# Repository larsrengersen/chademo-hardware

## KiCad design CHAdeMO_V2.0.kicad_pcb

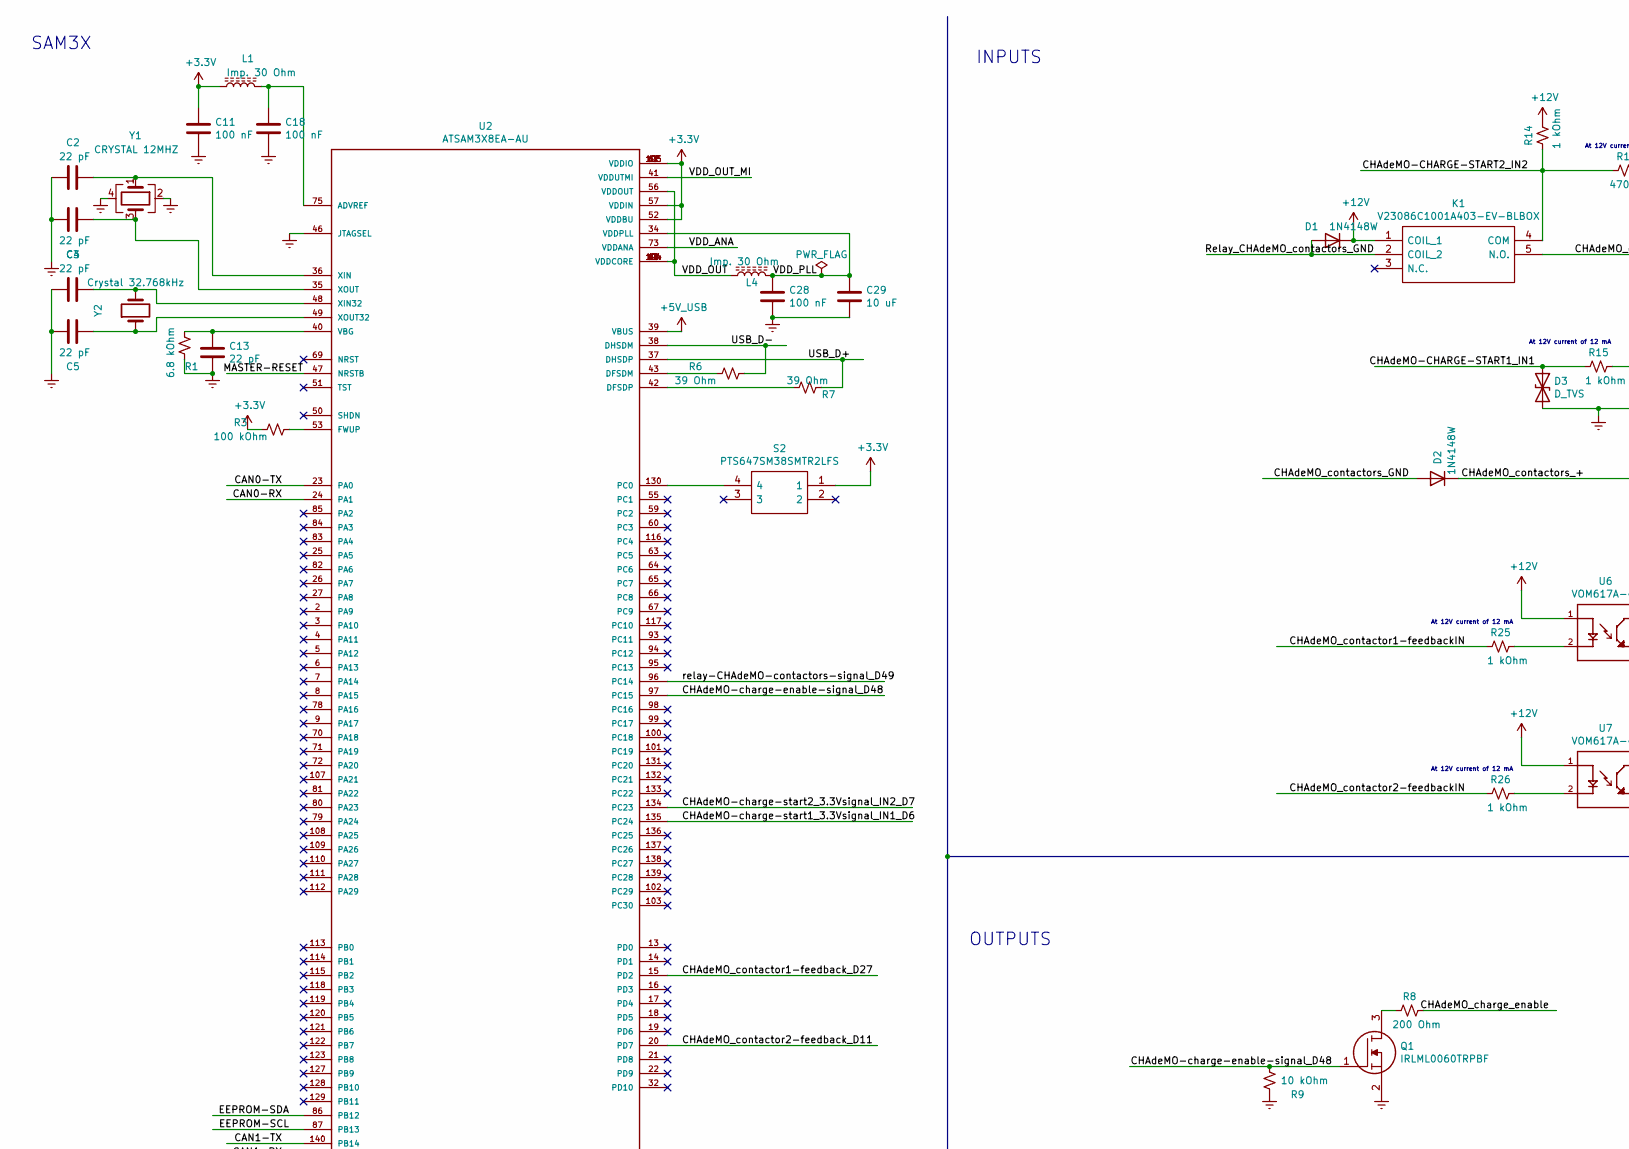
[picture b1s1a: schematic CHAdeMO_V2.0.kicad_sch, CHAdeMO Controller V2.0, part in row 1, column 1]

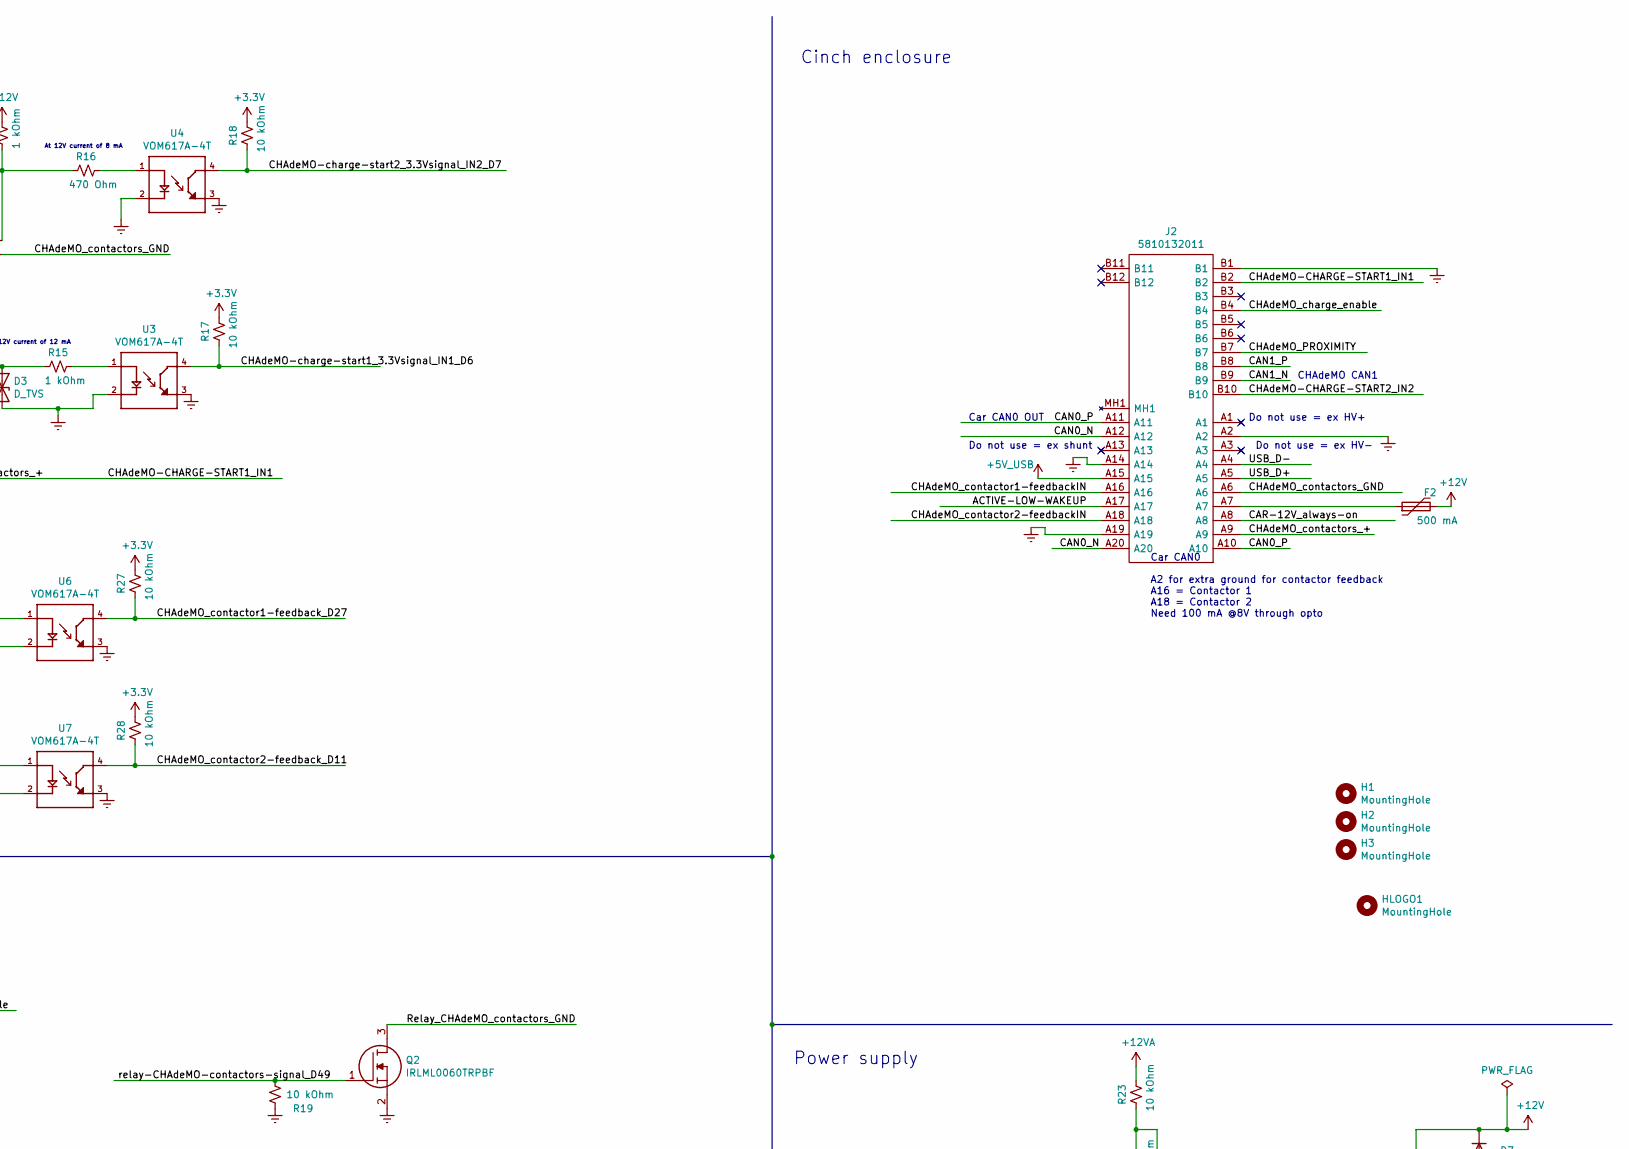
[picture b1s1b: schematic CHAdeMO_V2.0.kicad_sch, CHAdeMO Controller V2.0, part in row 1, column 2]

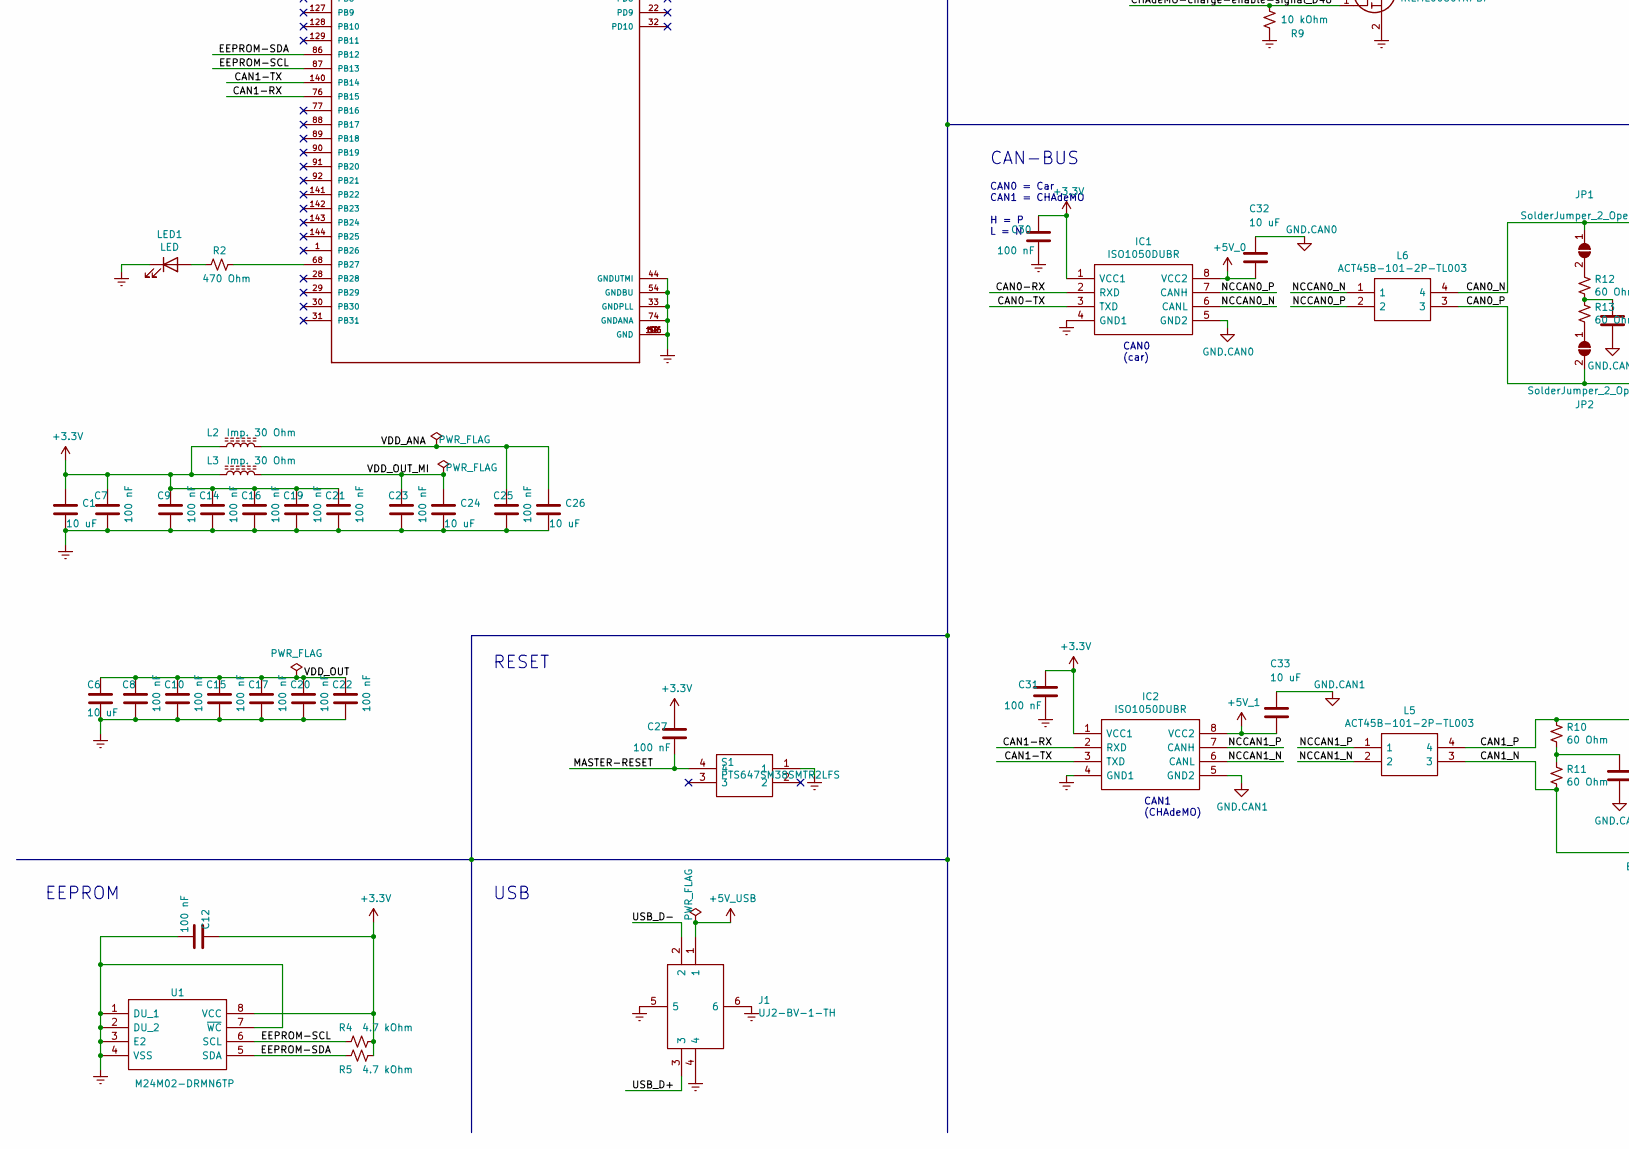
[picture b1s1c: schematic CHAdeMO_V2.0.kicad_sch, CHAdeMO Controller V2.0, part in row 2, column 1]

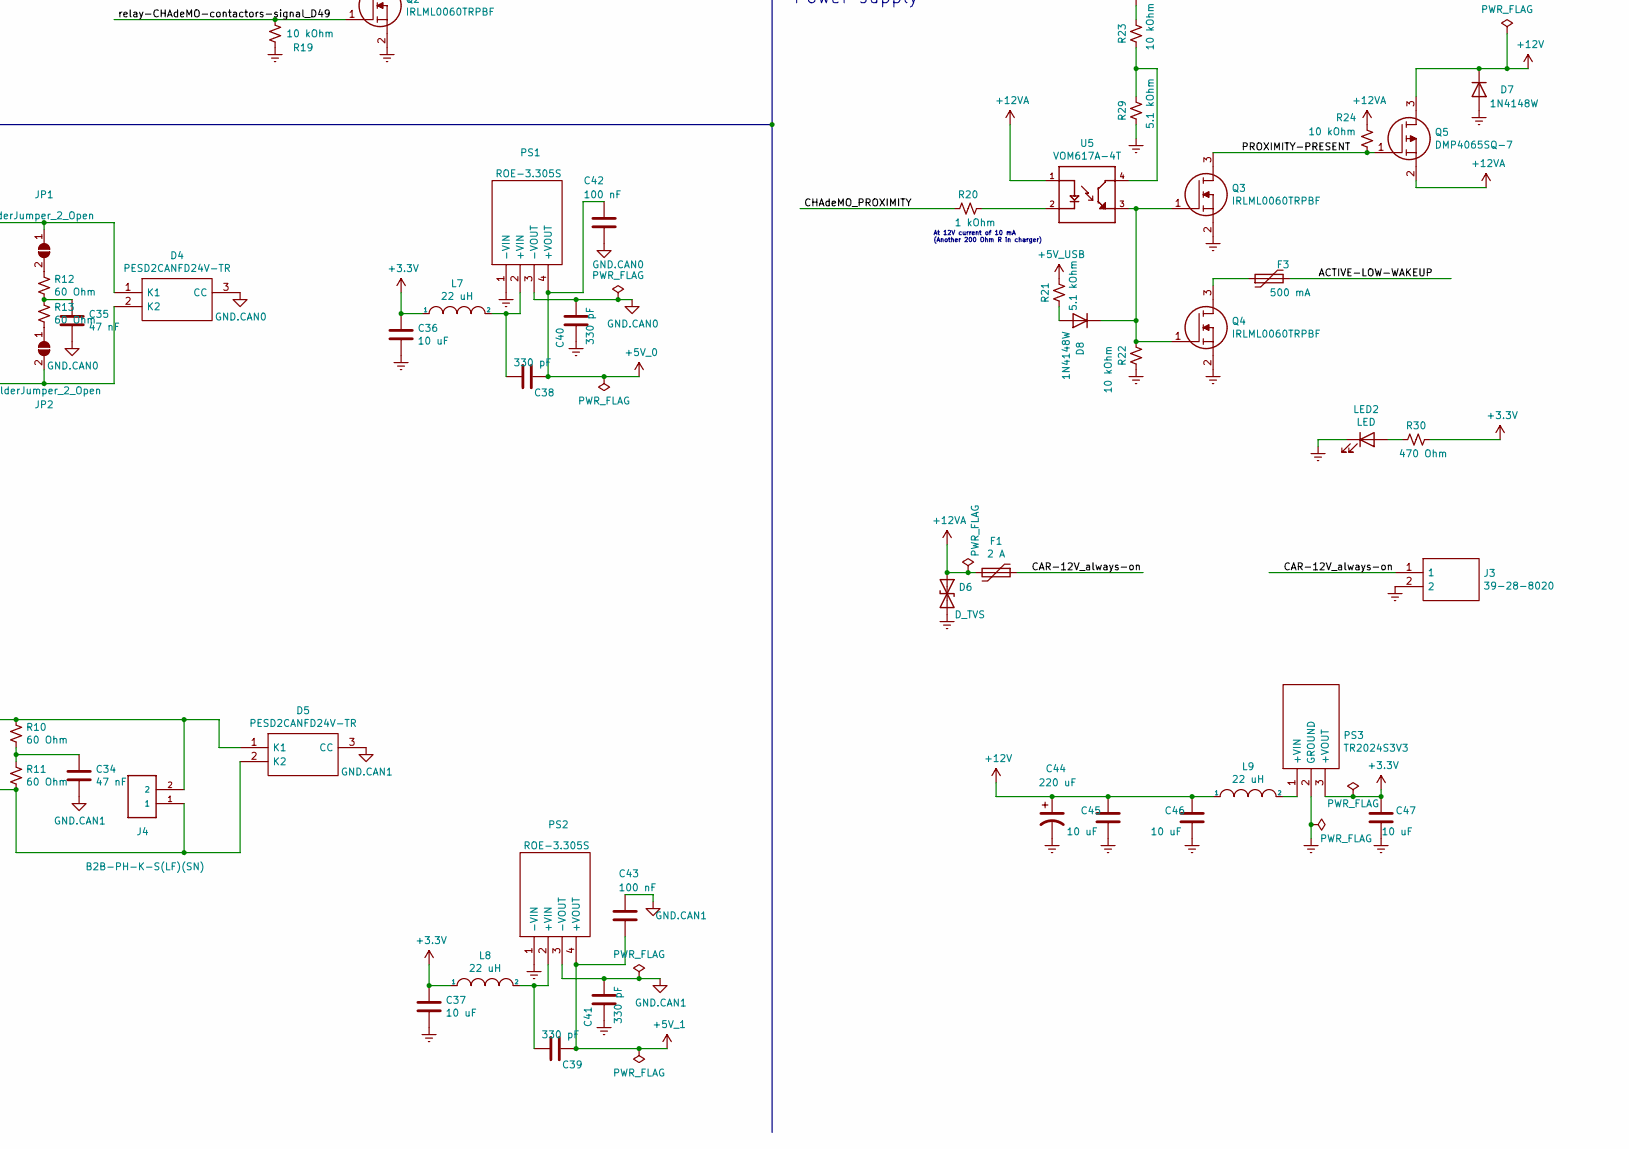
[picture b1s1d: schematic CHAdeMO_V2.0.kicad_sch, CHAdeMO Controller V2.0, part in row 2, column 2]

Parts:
C1, C6, C24, C26, C29, C32, C33, C36, C37, C45, C46, C47: 10 uF; C_1206_3216Metric; Manufacturer_Part_Number CL31A106KBHNNNE; JLC Footprint 1206
C2, C3, C4, C5, C13: 22 pF; C_0603_1608Metric; Manufacturer_Part_Number CL10C220JB8NNNC; JLC Footprint 0603
C7, C8, C9, C10, C11, C12, C14, C15, C16, C17, C18, C19, C20, C21, C22, C23, C25, C27, C28, C30, C31, C42, C43: 100 nF; C_1206_3216Metric; Manufacturer_Part_Number CL31B104KBCNNNC; JLC Footprint 1206
C34, C35: 47 nF; C_0603_1608Metric; Manufacturer_Part_Number CL10B473KB8NNNC; JLC Footprint 0603
C38, C39, C40, C41: 330 pF; C_0805_2012Metric; Manufacturer_Part_Number CL21B331KBANNNC; JLC Footprint 0805
C44: 220 uF; CAPAE1040X1050N; Manufacturer_Part_Number VEJ221M1HTR-1010; JLC Footprint SMD-ECAP-10x10
D1, D2, D7, D8: 1N4148W; D_SOD-123; Manufacturer_Part_Number 1N4148W; JLC Footprint SOD-123
D3, D6: D_TVS; DIOM5436X261N; Manufacturer_Part_Number SMBJ18CA; JLC Footprint SMB,DO-214AA
D4, D5: PESD2CANFD24V-TR; SOT95P230X110-3N; Mouser Part Number 771-PESD2CANFD24V-TR
F1: 2 A; FUSC7451X125N; Mouser Part Number 576-2920L200/24DR
F2, F3: 500 mA; Fuse_1206_3216Metric; Mouser Part Number 652-MF-NSHT050KX-2
H1, H2, H3: MountingHole; JLCPCB-ToolingHole
HLOGO1: MountingHole; EVcreate_2500
IC1, IC2: ISO1050DUBR; SOP254P1040X485-8N; Mouser Part Number 595-ISO1050DUBR
J1: UJ2-BV-1-TH; UJ2BV1TH; Manufacturer_Part_Number UJ2-BV-1-TH; Mouser Part Number 490-UJ2-BV-1-TH
J2: 5810132011; 5810132011_CHadeMO_v2; Manufacturer_Part_Number 5810132011; Mouser Part Number N/A
J3: 39-28-8020; SHDR2W125P550X420_2X1_540X960X1310P; Mouser Part Number 538-39-28-8020
J4: B2B-PH-K-S(LF)(SN); JST_B2B-PH-K-S(LF)(SN)
JP1, JP2: SolderJumper_2_Open; SolderJumper-2_P1.3mm_Open_RoundedPad1.0x1.5mm
K1: V23086C1001A403-EV-BLBOX; V23086C1001A403EVBLBOX; Mouser Part Number 655-1-1414761-0
L1, L2, L3, L4: Imp. 30 Ohm; L_0603_1608Metric; Manufacturer_Part_Number GZ1608D300TF; LCSC part number C24821
L5, L6: ACT45B-101-2P-TL003; ACT45B1012PTL003; Mouser Part Number 810-ACT45B1012PTL003
L7, L8, L9: 22 uH; INDPM4442X200N; Manufacturer_Part_Number MWSA0402S-220MT; JLC Footprint SMD-PIND-4.2x4.4x2.0_0.8x2.0
LED1, LED2: LED; LED_0603_1608Metric; Manufacturer_Part_Number 19-217/GHC-YR1S2/3T; JLC Footprint LED_0603
PS1, PS2: ROE-3.305S; ROE3305S; Mouser Part Number 919-ROE-3.305S
PS3: TR2024S3V3; Mouser Part Number 209-TR2024S3V3
Q1, Q2, Q3, Q4: IRLML0060TRPBF; SOT95P237X112-3N; Mouser Part Number 942-IRLML0060TRPBF
Q5: DMP4065SQ-7; SOT96P240X110-3N; Mouser Part Number 621-DMP4065SQ-7
R1: 6.8 kOhm; R_0805_2012Metric; Manufacturer_Part_Number 0805W8F6801T5E; JLC Footprint 0805
R2, R16, R30: 470 Ohm; R_0805_2012Metric; Manufacturer_Part_Number 0805W8F4700T5E; JLC Footprint 0805
R3: 100 kOhm; R_0603_1608Metric; Manufacturer_Part_Number 0603WAF1003T5E; JLC Footprint 0603
R4, R5: 4.7 kOhm; R_0805_2012Metric; Manufacturer_Part_Number 0805W8F4701T5E; JLC Footprint 0805
R6, R7: 39 Ohm; R_1206_3216Metric; Manufacturer_Part_Number 1206W4F390JT5E; JLC Footprint 1206
R8: 200 Ohm; R_0805_2012Metric; Manufacturer_Part_Number 0805W8F2000T5E; JLC Footprint 0805
R9, R19, R22, R23, R24, R27, R28: 10 kOhm; R_0805_2012Metric; Manufacturer_Part_Number ERJ-6ENF1002V; JLC Footprint 0402
R10, R11, R12, R13: 60 Ohm; R_1206_3216Metric; Manufacturer_Part_Number CRCW120660R0KNEAIF; JLC Footprint 1206
R14, R15, R20, R25, R26: 1 kOhm; R_0805_2012Metric; Manufacturer_Part_Number 0805W8F1001T5E; JLC Footprint 0805
R17, R18: 10 kOhm; R_0805_2012Metric; Manufacturer_Part_Number ERJ-6ENF1002V; JLC Footprint 0805
R21, R29: 5.1 kOhm; R_0805_2012Metric; Mouser Part Number 667-ERJ-6ENF5101V; JLC Footprint 0805
S1, S2: PTS647SM38SMTR2LFS; PTS647SK38SMTR2LFS; Mouser Part Number 611-PTS647SM38SMTR2L
U1: M24M02-DRMN6TP; SOIC127P600X175-8N; Manufacturer_Part_Number M24M02-DRMN6TP; JLC Footprint SOIC-8_3.9x4.9x1.27P
U2: ATSAM3X8EA-AU; QFP50P2200X2200X145-144N; Manufacturer_Part_Number ATSAM3X8EA-AU; LCSC C79305
U3, U4, U5, U6, U7: VOM617A-4T; VOM617A8X001T; Manufacturer_Part_Number VOM617A-4T; JLC Footprint SMD-4_4.6x6.5x2.54P
Y1: CRYSTAL 12MHZ; Crystal_SMD_3225-4Pin_3.2x2.5mm; Manufacturer_Part_Number X322512MSB4SI; JLC Footprint SMD-3225_4P
Y2: Crystal 32.768kHz; Crystal_SMD_3215-2Pin_3.2x1.5mm; Manufacturer_Part_Number Q13FC1350000400; JLC Footprint SMD-3215_2P

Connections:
+3V3: C1.1, C7.1, C9.1, C11.1, C12.1, C14.1, C16.1, C19.1, C21.1, C27.1, C30.1, C31.1, C36.1, C37.1, C47.1, IC1.1 (VCC1), IC2.1 (VCC1), L1.1, L2.1, L3.1, L7.1, L8.1, PS3.3 (+VOUT), R3.2, R4.1, R5.1, R17.1, R18.1, R27.1, R28.1, R30.1, S2.1, U1.8 (VCC), U2.11 (VDDIO), U2.52 (VDDBU), U2.57 (VDDIN), U2.62 (VDDIO), U2.105 (VDDIO), U2.125 (VDDIO)
+5V_0: C32.2, C38.1, C42.1, IC1.8 (VCC2), PS1.4 (+VOUT)
+5V_1: C33.2, C39.1, C43.2, IC2.8 (VCC2), PS2.4 (+VOUT)
+5V_USB: J1.1, J2.A15, R21.1, U2.39 (VBUS)
+12V: C44.1, C45.1, C46.1, D1.1 (K), D7.1 (K), F2.2, K1.1 (COIL_1), L9.1, Q5.3, R14.1, U6.1, U7.1
+12VA: D6.1 (A1), F1.2, Q5.2, R23.1, R24.1, U5.1
/ACTIVE-LOW-WAKEUP: F3.2, J2.A17
/CAN0-RX: IC1.2 (RXD), U2.24 (PA1)
/CAN0-TX: IC1.3 (TXD), U2.23 (PA0)
/CAN0_N: D4.1 (K1), J2.A12, J2.A20, JP1.1 (A), L6.4
/CAN0_P: D4.2 (K2), J2.A10, J2.A11, JP2.2 (B), L6.3
/CAN1-RX: IC2.2 (RXD), U2.76 (PB15)
/CAN1-TX: IC2.3 (TXD), U2.140 (PB14)
/CAN1_N: D5.2 (K2), J2.B9, J4.1, L5.3, R11.2
/CAN1_P: D5.1 (K1), J2.B8, J4.2, L5.4, R10.1
/CAR-12V_always-on: F1.1, J2.A8, J3.1
/CHAdeMO-CHARGE-START1_IN1: D2.1 (K), D3.1 (A1), J2.A9, J2.B2, R15.2
/CHAdeMO-CHARGE-START2_IN2: J2.B10, K1.4 (COM), R14.2, R16.2
/CHAdeMO-charge-enable-signal_D48: Q1.1, R9.1, U2.97 (PC15)
/CHAdeMO-charge-start1_3.3Vsignal_IN1_D6: R17.2, U2.135 (PC24), U3.4
/CHAdeMO-charge-start2_3.3Vsignal_IN2_D7: R18.2, U2.134 (PC23), U4.4
/CHAdeMO_PROXIMITY: J2.B7, R20.2
/CHAdeMO_charge_enable: J2.B4, R8.1
/CHAdeMO_contactor1-feedbackIN: J2.A16, R25.2
/CHAdeMO_contactor1-feedback_D27: R27.2, U2.15 (PD2), U6.4
/CHAdeMO_contactor2-feedbackIN: J2.A18, R26.2
/CHAdeMO_contactor2-feedback_D11: R28.2, U2.20 (PD7), U7.4
/CHAdeMO_contactors_GND: D2.2 (A), J2.A6, K1.5 (N.O.)
/EEPROM-SCL: R4.2, U1.6 (SCL), U2.87 (PB13)
/EEPROM-SDA: R5.2, U1.5 (SDA), U2.86 (PB12)
/MASTER-RESET: C27.2, S1.4, U2.47 (NRSTB)
/NCCAN0_N: IC1.6 (CANL), L6.1
/NCCAN0_P: IC1.7 (CANH), L6.2
/NCCAN1_N: IC2.6 (CANL), L5.2
/NCCAN1_P: IC2.7 (CANH), L5.1
/PROXIMITY-PRESENT: Q3.3, Q5.1, R24.2
/Relay_CHAdeMO_contactors_GND: D1.2 (A), K1.2 (COIL_2), Q2.3
/USB_D+: J1.3, J2.A5, R7.1, U2.37 (DHSDP)
/USB_D-: J1.2, J2.A4, R6.1, U2.38 (DHSDM)
/VDD_ANA: C25.1, C26.1, L2.2, U2.73 (VDDANA)
/VDD_OUT: C6.1, C8.1, C10.1, C15.1, C17.1, C20.1, C22.1, L4.1, U2.10 (VDDCORE), U2.45 (VDDCORE), U2.56 (VDDOUT), U2.61 (VDDCORE), U2.104 (VDDCORE), U2.124 (VDDCORE)
/VDD_OUT_MI: C23.1, C24.1, L3.2, U2.41 (VDDUTMI)
/VDD_PLL: C28.1, C29.1, L4.2, U2.34 (VDDPLL)
/relay-CHAdeMO-contactors-signal_D49: Q2.1, R19.1, U2.96 (PC14)
Earth: C1.2, C2.2, C3.2, C4.2, C5.2, C6.2, C7.2, C8.2, C9.2, C10.2, C11.2, C12.2, C13.2, C14.2, C15.2, C16.2, C17.2, C18.2, C19.2, C20.2, C21.2, C22.2, C23.2, C24.2, C25.2, C26.2, C28.2, C29.2, C30.2, C31.2, C36.2, C37.2, C40.1, C41.1, C44.2, C45.2, C46.2, C47.2, D3.2 (A2), D6.2 (A2), D7.2 (A), IC1.4 (GND1), IC2.4 (GND1), J1.4, J1.5, J1.6, J2.A2, J2.A14, J2.A19, J2.B1, J3.2, LED1.1 (K), LED2.1 (K), PS1.1 (-VIN), PS2.1 (-VIN), PS3.2 (GROUND), Q1.2, Q2.2, Q3.2, Q4.2, R1.1, R9.2, R19.2, R22.2, R29.2, S1.1, U1.1 (DU_1), U1.2 (DU_2), U1.3 (E2), U1.4 (VSS), U1.7 (~WC), U2.12 (GND), U2.33 (GNDPLL), U2.44 (GNDUTMI), U2.46 (JTAGSEL), U2.54 (GNDBU), U2.58 (GND), U2.74 (GNDANA), U2.106 (GND), U2.126 (GND), U3.2, U3.3, U4.2, U4.3, U6.3, U7.3, Y1.2, Y1.4
GND_CAN0: C32.1, C35.2, C40.2, C42.2, D4.3 (CC), IC1.5 (GND2), PS1.3 (-VOUT)
GND_CAN1: C33.1, C34.2, C41.2, C43.1, D5.3 (CC), IC2.5 (GND2), PS2.3 (-VOUT)
unnamed: C2.1, U2.36 (XIN), Y1.1
unnamed: C3.1, U2.35 (XOUT), Y1.3
unnamed: C4.1, U2.48 (XIN32), Y2.2
unnamed: C5.1, U2.49 (XOUT32), Y2.1
unnamed: C13.1, R1.2, U2.40 (VBG)
unnamed: C18.1, L1.2, U2.75 (ADVREF)
unnamed: C34.1, R10.2, R11.1
unnamed: C35.1, R12.2, R13.1
unnamed: C38.2, L7.2, PS1.2 (+VIN)
unnamed: C39.2, L8.2, PS2.2 (+VIN)
unnamed: D8.1 (K), Q3.1, Q4.1, R22.1, U5.3
unnamed: D8.2 (A), R21.2
unnamed: F2.1, J2.A7
unnamed: F3.1, Q4.3
unnamed: JP1.2 (B), R12.1
unnamed: JP2.1 (A), R13.2
unnamed: L9.2, PS3.1 (+VIN)
unnamed: LED1.2 (A), R2.2
unnamed: LED2.2 (A), R30.2
unnamed: Q1.3, R8.2
unnamed: R2.1, U2.68 (PB27)
unnamed: R3.1, U2.53 (FWUP)
unnamed: R6.2, U2.43 (DFSDM)
unnamed: R7.2, U2.42 (DFSDP)
unnamed: R15.1, U3.1
unnamed: R16.1, U4.1
unnamed: R20.1, U5.2
unnamed: R23.2, R29.1, U5.4
unnamed: R25.1, U6.2
unnamed: R26.1, U7.2
unnamed: S2.4, U2.130 (PC0)

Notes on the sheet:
At 12V current of 10 mA (Another 200 Ohm R in charger)
At 12V current of 12 mA
RESET
OUTPUTS
At 12V current of 8 mA
CHAdeMO CAN1
Car CAN0 OUT
CAN0 (car)
Do not use = ex HV-
USB
A2 for extra ground for contactor feedback A16 = Contactor 1 A18 = Contactor 2 Need 100 mA @8V through opto
Do not use = ex HV+
Power supply
EEPROM
Car CAN0
SAM3X
Do not use = ex shunt
CAN-BUS
INPUTS
Cinch enclosure
CAN1 (CHAdeMO)
CAN0 = Car CAN1 = CHAdeMO H = P L = N

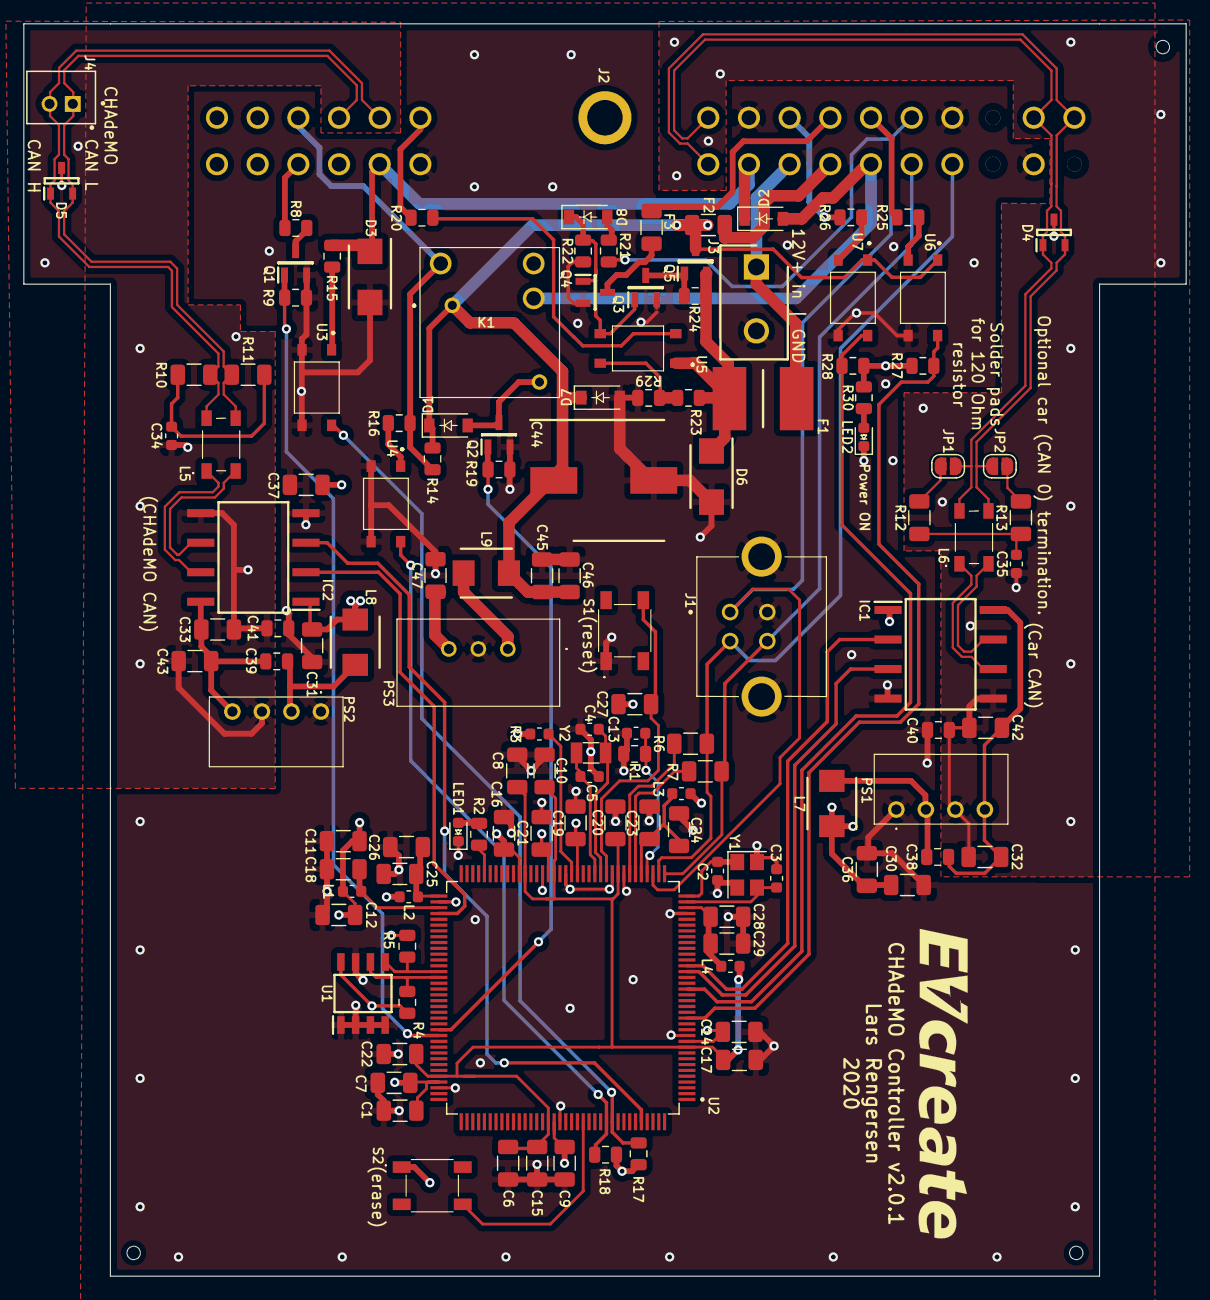
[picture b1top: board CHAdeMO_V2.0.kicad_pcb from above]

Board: 4 copper layers, 100.0 x 107.7 mm, 131 parts (0 on the bottom side), 78 nets.

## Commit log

2021-01-18 PCB V2.0.1 design
2021-05-20 Fixed references to library
2021-12-21 Moved to LQFP100 chip
2021-12-21 Initial
2021-12-21 Test fit entire Flip&Click board
2021-12-21 Review 2.0.1 result and add SAM3x stp
2021-12-22 Ordered 2.0.2 22/12 at JLCPCB
2021-12-22 Dummy footprints
    For stencil with cutouts for JLCPCB placed components
2021-12-23 V2.0.3 ordered at JLCPCB 23/12
2022-02-24 2.0.3 Ball
2022-02-24 Prepare for 2.0.4
2022-02-24 cache
2024-03-03 2.0.4
2026-03-20 Create LICENSE
